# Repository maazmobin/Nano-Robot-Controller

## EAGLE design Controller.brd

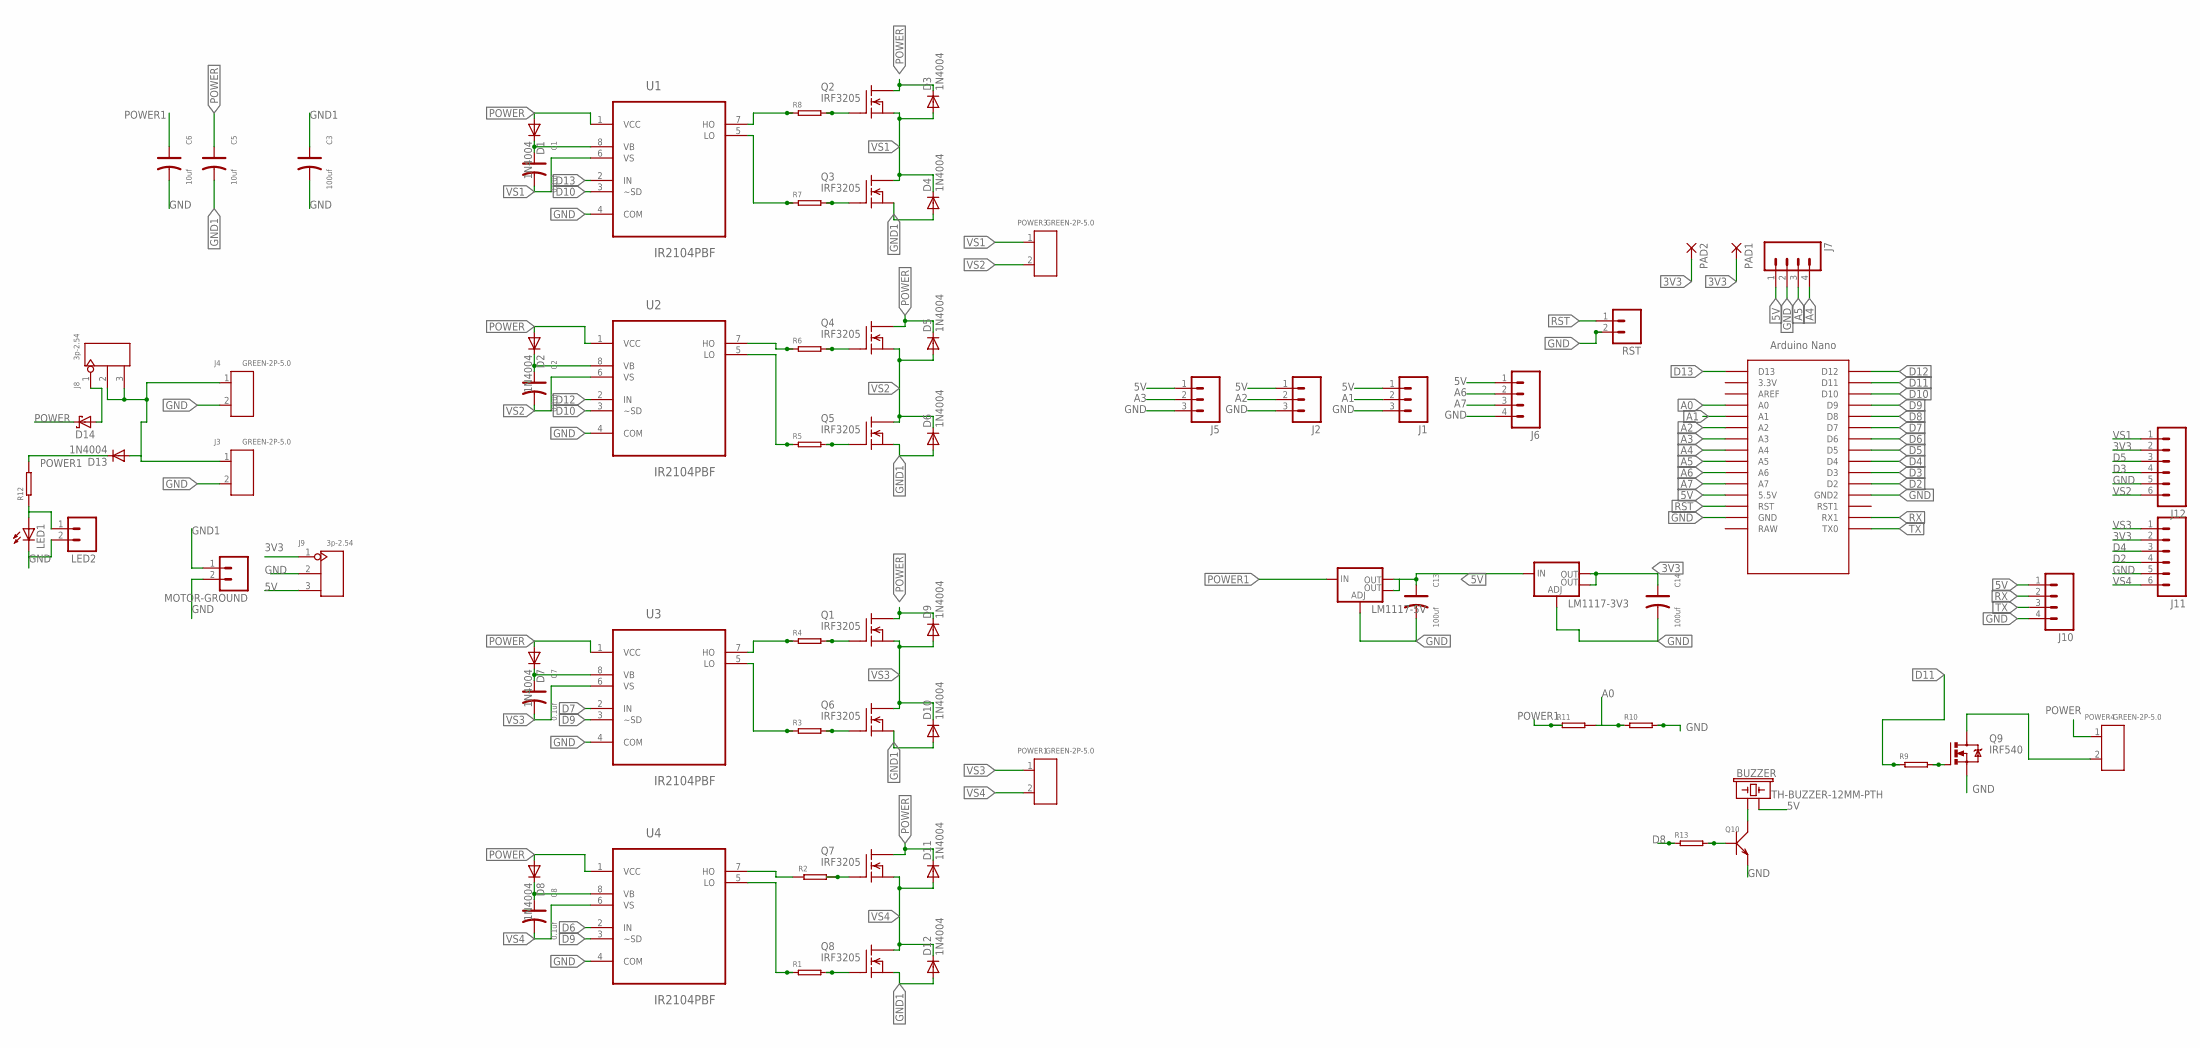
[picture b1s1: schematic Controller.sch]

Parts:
BUZZER: TH-BUZZER-12MM-PTH; BUZZER-12MM
C1, C2, C7, C8: 0.1uf; PC-D5.3MM
C3, C13, C14: 100uf; PC-D5.3MM
C5, C6: 10uf; PC-D5.3MM
D1, D2, D3, D4, D5, D6, D7, D8, D9, D10, D11, D12, D13: 1N4004; DO41-10
D14: SCHOTTKY-DIODEDO201T15; DO201T15
J1, J2, J5: M03POLAR; MOLEX-1X3
J3, J4: GREEN-2P-5.0; H2-5.0-10.5X8.0MM
J6, J7, J10: M04POLAR; MOLEX-1X4
J8, J9: 3p-2.54; H3-2.54
J11, J12: M06POLAR; MOLEX-1X6
LED1: LEDCHIPLED_0603; CHIPLED_0603
LED2: M02PTH; 1X02
LM1117-3V3, LM1117-5V: V_REG_LM1117SOT223; SOT223
MOTOR-GROUND: M02PTH; 1X02
PAD1, PAD2: 2,15/1,0
POWER1, POWER3, POWER4: GREEN-2P-5.0; H2-5.0-10.5X8.0MM
Q1, Q2, Q3, Q4, Q5, Q6, Q7, Q8: IRF3205; TO220
Q9: IRF540; TO220BV
Q10: SMD-TRANSISTOR-NPN-SOT-23; SOT-23
R1, R2, R3, R4, R5, R6, R7, R8, R9, R10, R11, R12, R13: SMD-RESISTOR-0603; R0603
RST: M02PTH; 1X02
U1, U2, U3, U4: IR2104PBF; DIP254P762X533-8
U$1: NANO

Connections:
3V3: C14.+, J9.1, J11.2, J12.2, LM1117-3V3.2 (OUT), LM1117-3V3.4 (OUT), PAD1.1, PAD2.1
5V: BUZZER.- (2), C13.+, J1.1, J2.1, J5.1, J6.1, J7.1, J9.3, J10.1, LM1117-3V3.3 (IN), LM1117-5V.2 (OUT), LM1117-5V.4 (OUT), U$1.5V (5.5V)
A0: R10.1, R11.2, U$1.A0
A1: J1.2, U$1.A1
A2: J2.2, U$1.A2
A3: J5.2, U$1.A3
A4: J7.4, U$1.A4
A5: J7.3, U$1.A5
A6: J6.2, U$1.A6
A7: J6.3, U$1.A7
D2: J11.4, U$1.D2
D3: J12.4, U$1.D3
D4: J11.3, U$1.D4
D5: J12.3, U$1.D5
D6: U4.2 (IN), U$1.D6
D7: U3.2 (IN), U$1.D7
D8: R13.1, U$1.D8
D9: U3.3 (~SD), U4.3 (~SD), U$1.D9
D10: U1.3 (~SD), U2.3 (~SD), U$1.D10
D11: R9.1, U$1.D11
D12: U2.2 (IN), U$1.D12
D13: U1.2 (IN), U$1.D13
GND: C3.-, C6.-, C13.-, C14.-, J1.3, J2.3, J3.2, J4.2, J5.3, J6.4, J7.2, J9.2, J10.4, J11.5, J12.5, LED1.C, LED2.2, LM1117-3V3.1 (ADJ), LM1117-5V.1 (ADJ), MOTOR-GROUND.2, Q9.S, Q10.2 (E), R10.2, RST.2, U1.4 (COM), U2.4 (COM), U3.4 (COM), U4.4 (COM), U$1.GND, U$1.GND1 (GND2)
GND1: C3.+, C5.-, D4.A, D6.A, D10.A, D12.A, MOTOR-GROUND.1, Q3.3 (S), Q5.3 (S), Q6.3 (S), Q8.3 (S)
unnamed: Q3.1 (G), R7.2
unnamed: C1.+, D1.C, U1.8 (VB)
unnamed: Q4.1 (G), R6.2
unnamed: C2.+, D2.C, U2.8 (VB)
unnamed: Q5.1 (G), R5.2
unnamed: Q2.1 (G), R8.2
unnamed: R8.1, U1.7 (HO)
unnamed: R7.1, U1.5 (LO)
unnamed: R6.1, U2.7 (HO)
unnamed: R5.1, U2.5 (LO)
unnamed: C7.+, D7.C, U3.8 (VB)
unnamed: C8.+, D8.C, U4.8 (VB)
unnamed: Q7.1 (G), R2.2
unnamed: Q8.1 (G), R1.2
unnamed: Q1.1 (G), R4.2
unnamed: R4.1, U3.7 (HO)
unnamed: R3.1, U3.5 (LO)
unnamed: R2.1, U4.7 (HO)
unnamed: R1.1, U4.5 (LO)
unnamed: Q6.1 (G), R3.2
unnamed: D13.A, J3.1, J4.1, J8.2, J8.3
unnamed: Q9.G, R9.2
unnamed: LED1.A, LED2.1, R12.1
unnamed: POWER4.2, Q9.D
unnamed: Q10.1 (B), R13.2
unnamed: BUZZER.+ (1), Q10.3 (C)
unnamed: D14.A, J8.1
POWER: C5.+, D1.A, D2.A, D3.C, D5.C, D7.A, D8.A, D9.C, D11.C, D14.C, POWER4.1, Q1.2 (D), Q2.2 (D), Q4.2 (D), Q7.2 (D), U1.1 (VCC), U2.1 (VCC), U3.1 (VCC), U4.1 (VCC)
POWER1: C6.+, D13.C, LM1117-5V.3 (IN), R11.1, R12.2
RST: RST.1, U$1.RST
RX: J10.2, U$1.RX1
TX: J10.3, U$1.TX0
VS1: C1.-, D3.A, D4.C, J12.1, POWER3.1, Q2.3 (S), Q3.2 (D), U1.6 (VS)
VS2: C2.-, D5.A, D6.C, J12.6, POWER3.2, Q4.3 (S), Q5.2 (D), U2.6 (VS)
VS3: C7.-, D9.A, D10.C, J11.1, POWER1.1, Q1.3 (S), Q6.2 (D), U3.6 (VS)
VS4: C8.-, D11.A, D12.C, J11.6, POWER1.2, Q7.3 (S), Q8.2 (D), U4.6 (VS)

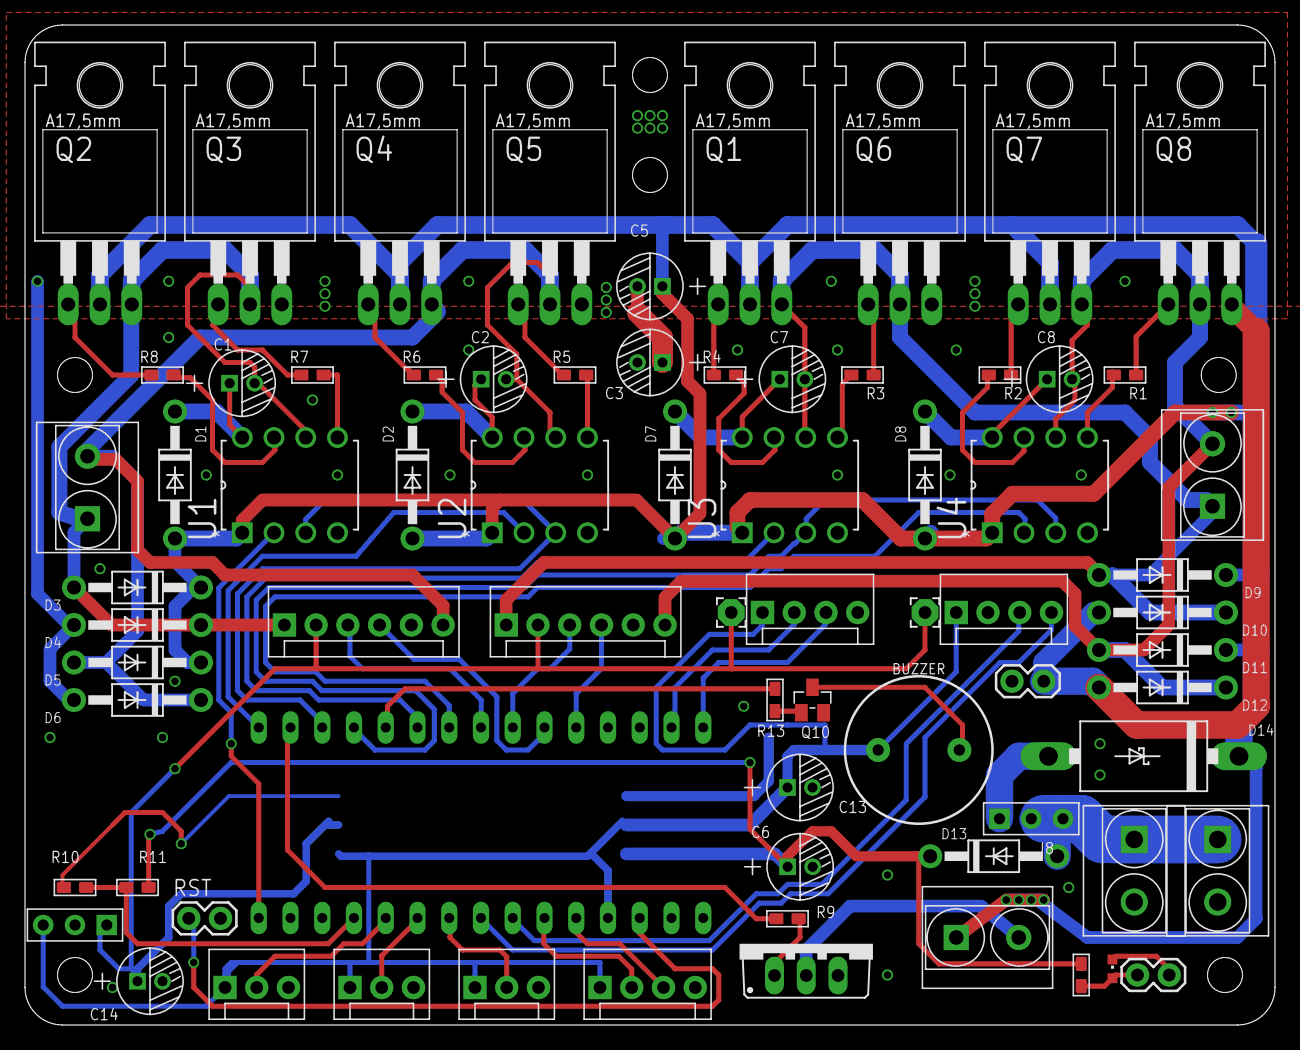
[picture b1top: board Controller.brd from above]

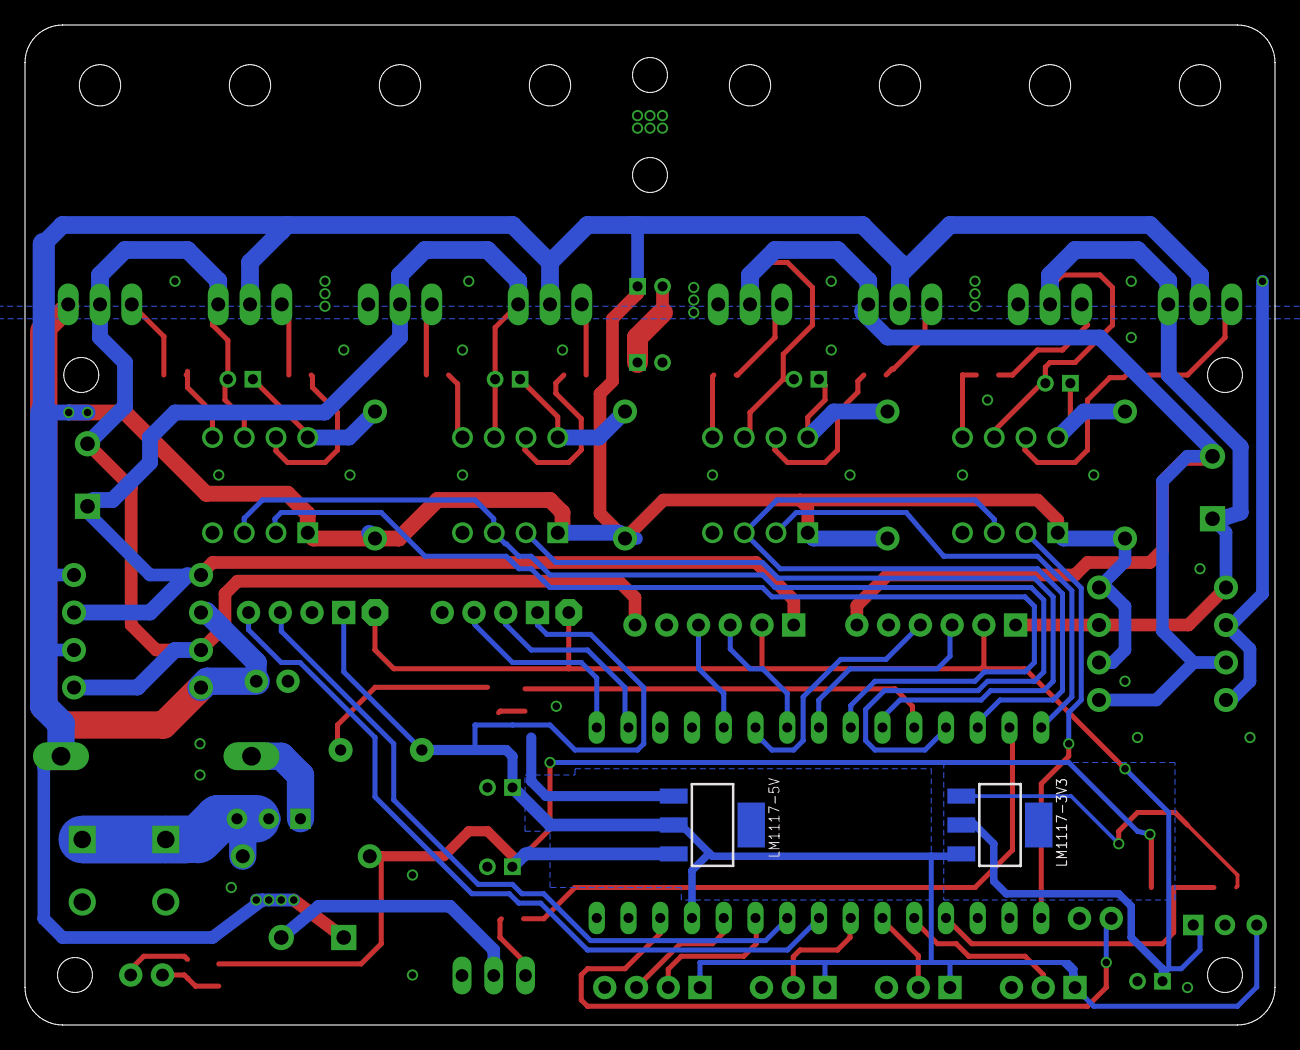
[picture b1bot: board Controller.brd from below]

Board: 2 copper layers, 100.0 x 80.0 mm, 75 parts (2 on the bottom side), 60 nets.

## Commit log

2017-10-17 :space_invader: Added .gitattributes & .gitignore files
2017-10-18 COMPLETED review required
2017-10-18 review 1
2017-10-18 review 2 done
2017-10-18 Review 3
2017-10-19 REVIEW 4

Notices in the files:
parts and their libraries:
SparkFun-Connectors: Licensing: Creative Commons ShareAlike 4.0 International - https://creativecommons.org/licenses/by-sa/4.0
